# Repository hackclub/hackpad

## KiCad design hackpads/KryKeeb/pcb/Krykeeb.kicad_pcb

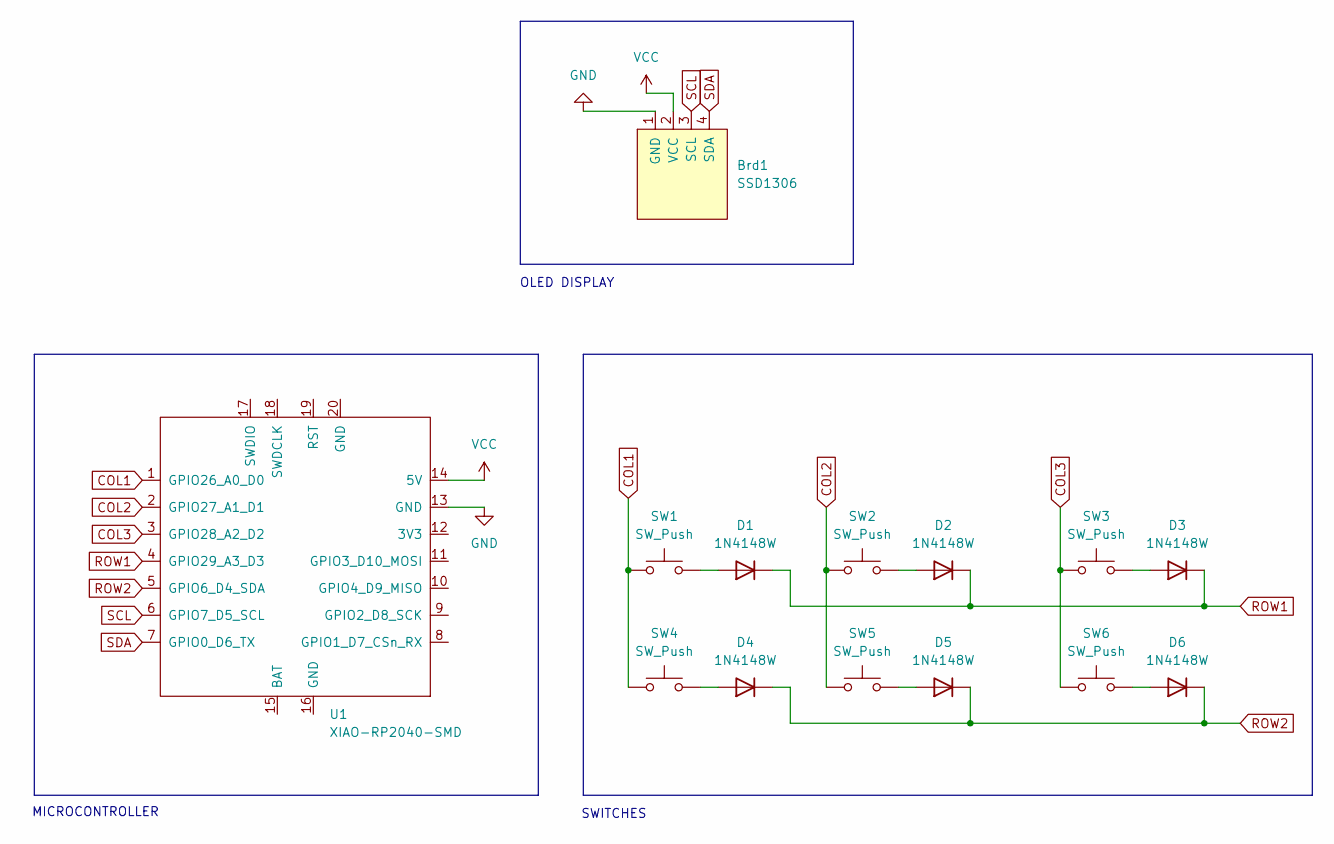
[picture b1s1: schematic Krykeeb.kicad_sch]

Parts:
Brd1: SSD1306; 128x64OLED
D1, D2, D3, D4, D5, D6: 1N4148W; D_A-405_P7.62mm_Horizontal
SW1, SW2, SW3, SW4, SW5, SW6: SW_Push; SW_Cherry_MX_1.00u_PCB
U1: XIAO-RP2040-SMD; MOUDLE14P-2.54-21X17.8MM

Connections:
COL1: SW1.1, SW4.1, U1.1 (GPIO26_A0_D0)
COL2: SW2.1, SW5.1, U1.2 (GPIO27_A1_D1)
COL3: SW3.1, SW6.1, U1.3 (GPIO28_A2_D2)
GND: Brd1.1 (GND), U1.13 (GND)
unnamed: D1.2 (A), SW1.2
unnamed: D2.2 (A), SW2.2
unnamed: D3.2 (A), SW3.2
unnamed: D4.2 (A), SW4.2
unnamed: D5.2 (A), SW5.2
unnamed: D6.2 (A), SW6.2
ROW1: D1.1 (K), D2.1 (K), D3.1 (K), U1.4 (GPIO29_A3_D3)
ROW2: D4.1 (K), D5.1 (K), D6.1 (K), U1.5 (GPIO6_D4_SDA)
SCL: Brd1.3 (SCL), U1.6 (GPIO7_D5_SCL)
SDA: Brd1.4 (SDA), U1.7 (GPIO0_D6_TX)
VCC: Brd1.2 (VCC), U1.14 (5V)

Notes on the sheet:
OLED DISPLAY
MICROCONTROLLER
SWITCHES

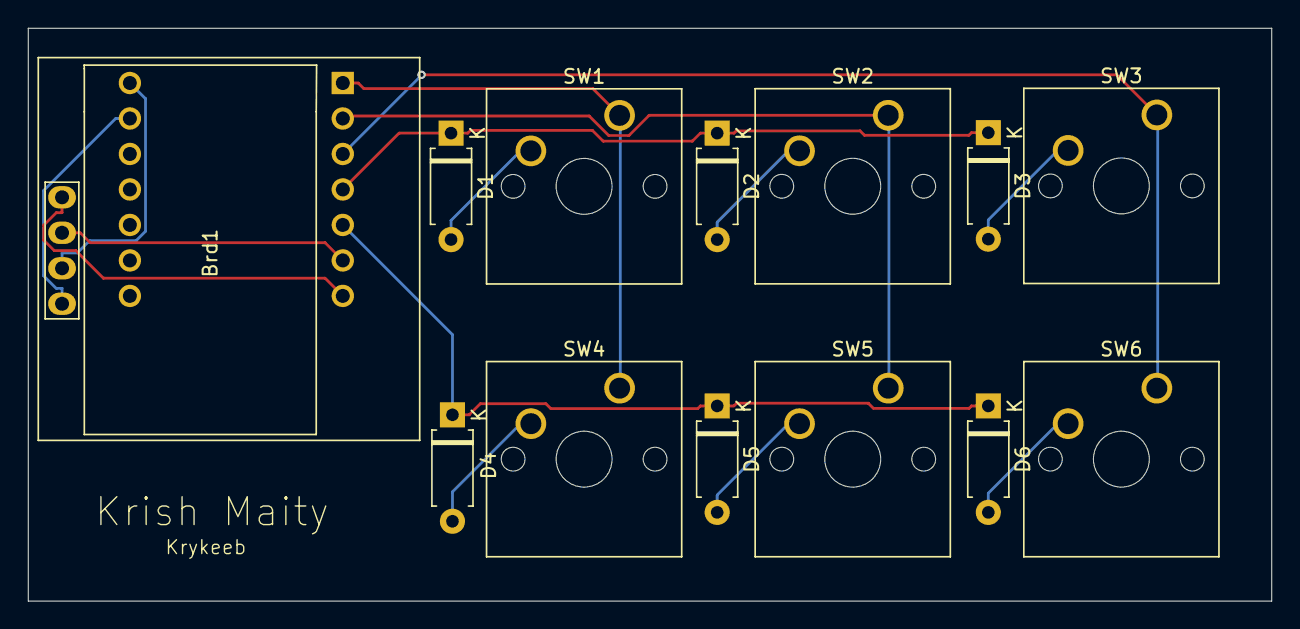
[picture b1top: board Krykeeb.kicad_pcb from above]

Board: 2 copper layers, 89.0 x 41.0 mm, 14 parts (1 on the bottom side), 15 nets.

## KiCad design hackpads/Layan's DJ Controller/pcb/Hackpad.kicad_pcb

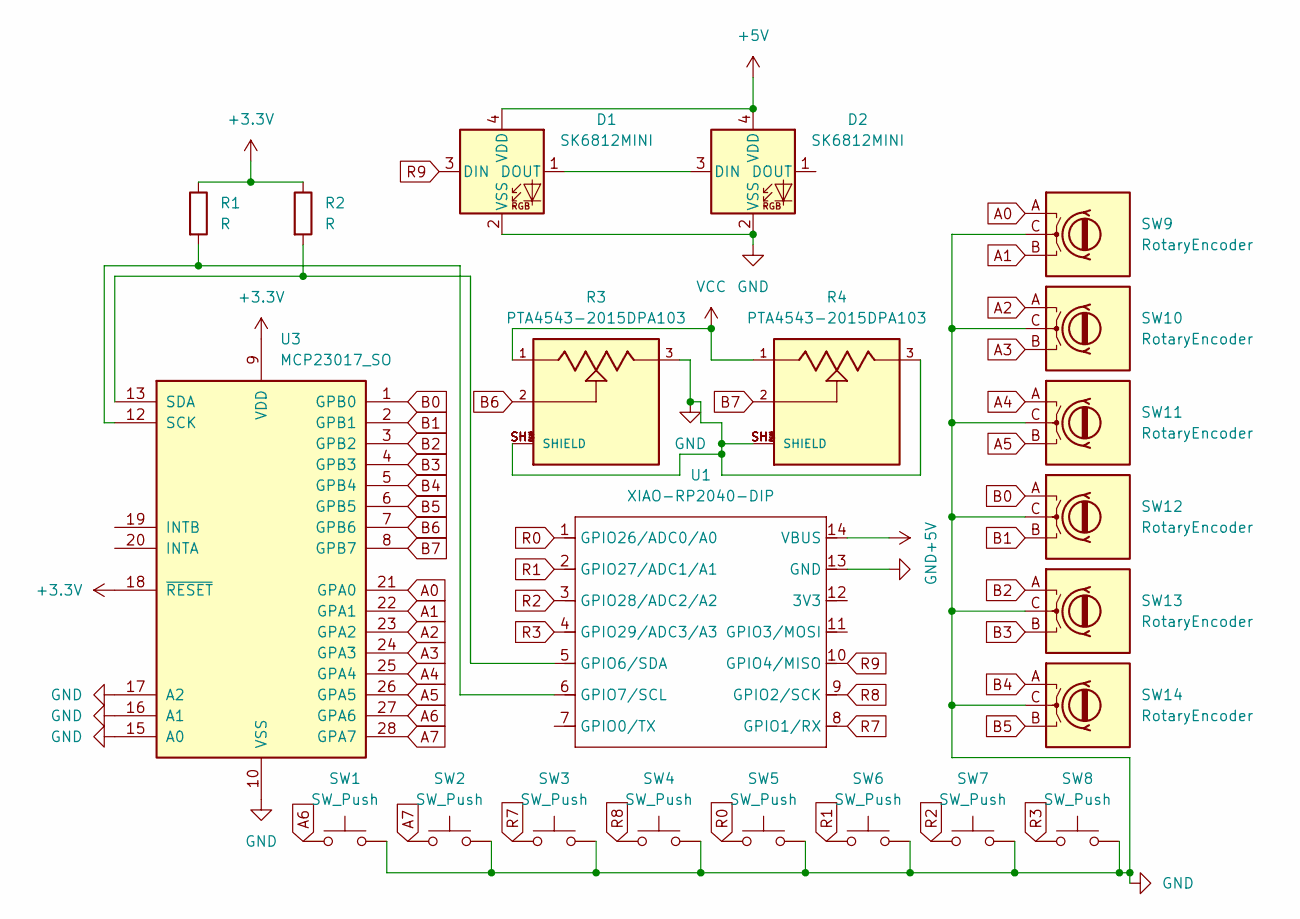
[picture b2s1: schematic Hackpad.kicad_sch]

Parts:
D1, D2: SK6812MINI; LED_SK6812MINI_PLCC4_3.5x3.5mm_P1.75mm
R1, R2: R; R_Axial_DIN0204_L3.6mm_D1.6mm_P7.62mm_Horizontal
R3, R4: PTA4543-2015DPA103; TRIM_PTA4543-2015DPA103; PARTREV 04/21
SW1, SW2, SW3, SW4, SW5, SW6, SW7, SW8: SW_Push; SW_Cherry_MX_1.00u_PCB
SW9, SW10, SW11, SW12, SW13, SW14: RotaryEncoder; RotaryEncoder_Alps_EC11E_Vertical_H20mm
U1: XIAO-RP2040-DIP
U3: MCP23017_SO; SOIC-28W_7.5x17.9mm_P1.27mm

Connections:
+3.3V: R1.1, R2.1, U3.9 (VDD), U3.18 (~RESET)
+5V: D1.4 (VDD), D2.4 (VDD), U1.14 (VBUS)
A0: SW9.A, U3.21 (GPA0)
A1: SW9.B, U3.22 (GPA1)
A2: SW10.A, U3.23 (GPA2)
A3: SW10.B, U3.24 (GPA3)
A4: SW11.A, U3.25 (GPA4)
A5: SW11.B, U3.26 (GPA5)
A6: SW1.1, U3.27 (GPA6)
A7: SW2.1, U3.28 (GPA7)
B0: SW12.A, U3.1 (GPB0)
B1: SW12.B, U3.2 (GPB1)
B2: SW13.A, U3.3 (GPB2)
B3: SW13.B, U3.4 (GPB3)
B4: SW14.A, U3.5 (GPB4)
B5: SW14.B, U3.6 (GPB5)
B6: R3.2, U3.7 (GPB6)
B7: R4.2, U3.8 (GPB7)
GND: D1.2 (VSS), D2.2 (VSS), R3.3, R3.SH1 (SHIELD), R3.SH2 (SHIELD), R3.SH3 (SHIELD), R3.SH4 (SHIELD), R4.3, R4.SH1 (SHIELD), R4.SH2 (SHIELD), R4.SH3 (SHIELD), R4.SH4 (SHIELD), SW1.2, SW2.2, SW3.2, SW4.2, SW5.2, SW6.2, SW7.2, SW8.2, SW9.C, SW10.C, SW11.C, SW12.C, SW13.C, SW14.C, U1.13 (GND), U3.10 (VSS), U3.15 (A0), U3.16 (A1), U3.17 (A2)
unnamed: D1.1 (DOUT), D2.3 (DIN)
unnamed: R2.2, U1.5 (GPIO6/SDA), U3.13 (SDA)
unnamed: R1.2, U1.6 (GPIO7/SCL), U3.12 (SCK)
R0: SW5.1, U1.1 (GPIO26/ADC0/A0)
R1: SW6.1, U1.2 (GPIO27/ADC1/A1)
R2: SW7.1, U1.3 (GPIO28/ADC2/A2)
R3: SW8.1, U1.4 (GPIO29/ADC3/A3)
R7: SW3.1, U1.8 (GPIO1/RX)
R8: SW4.1, U1.9 (GPIO2/SCK)
R9: D1.3 (DIN), U1.10 (GPIO4/MISO)
VCC: R3.1, R4.1

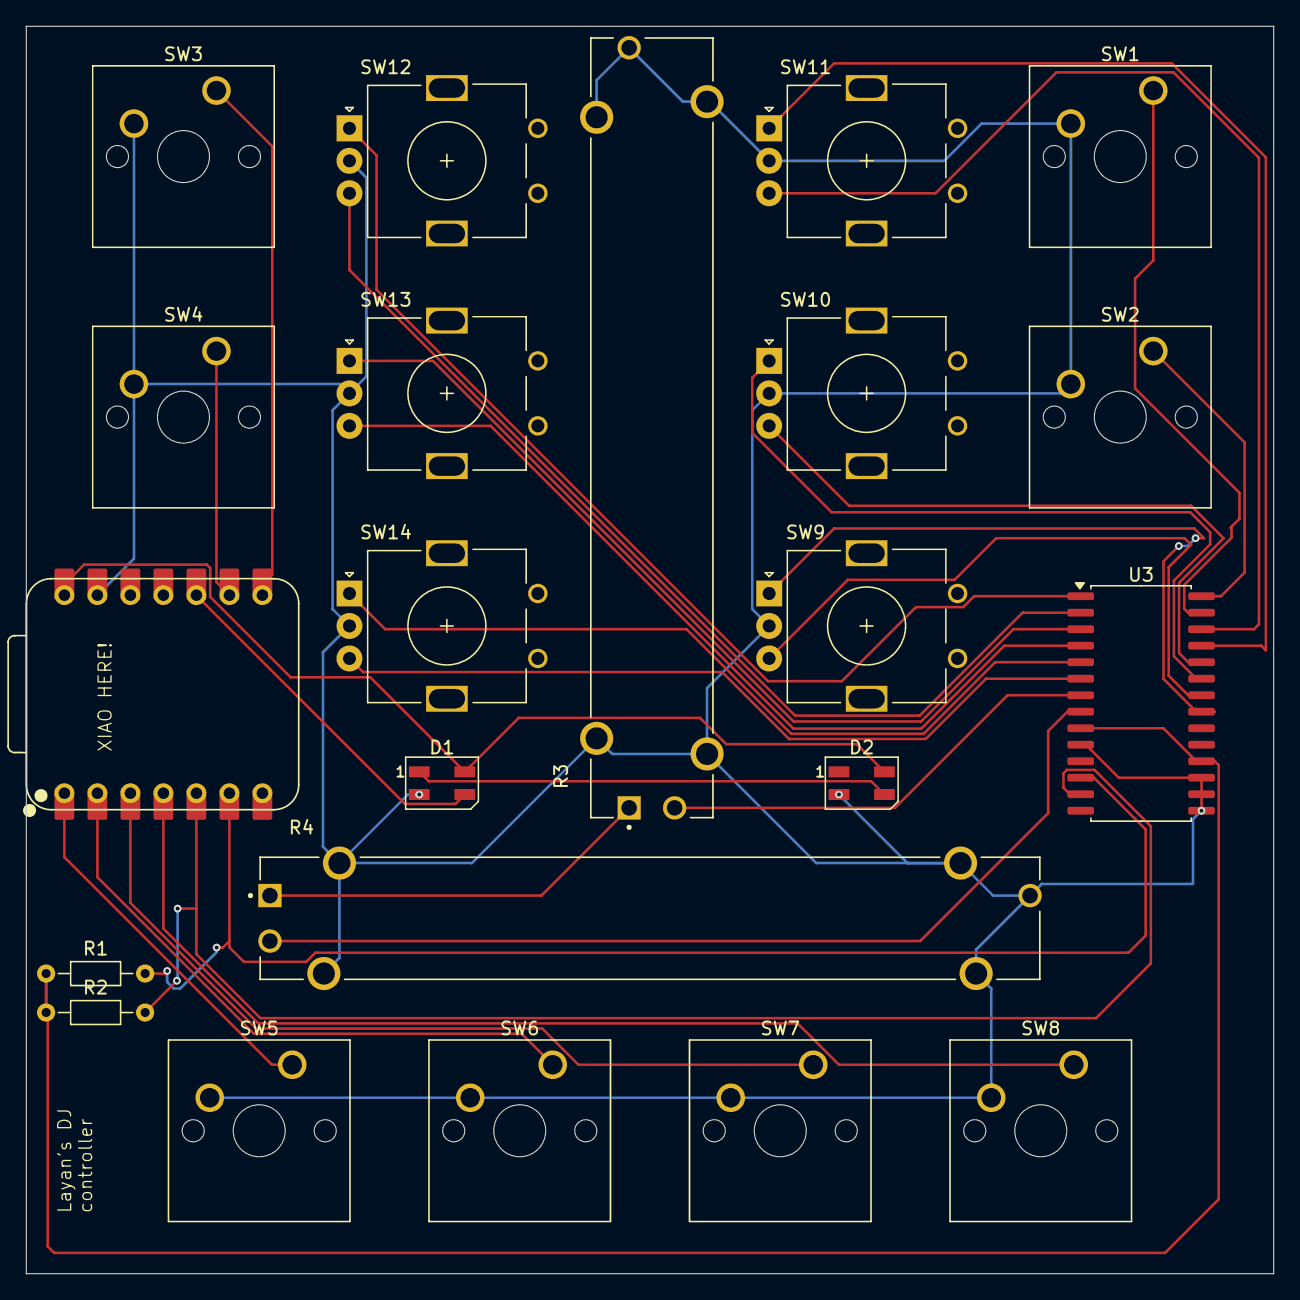
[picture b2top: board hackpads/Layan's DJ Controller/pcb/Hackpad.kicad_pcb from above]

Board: 2 copper layers, 96.0 x 96.0 mm, 22 parts (0 on the bottom side), 30 nets.

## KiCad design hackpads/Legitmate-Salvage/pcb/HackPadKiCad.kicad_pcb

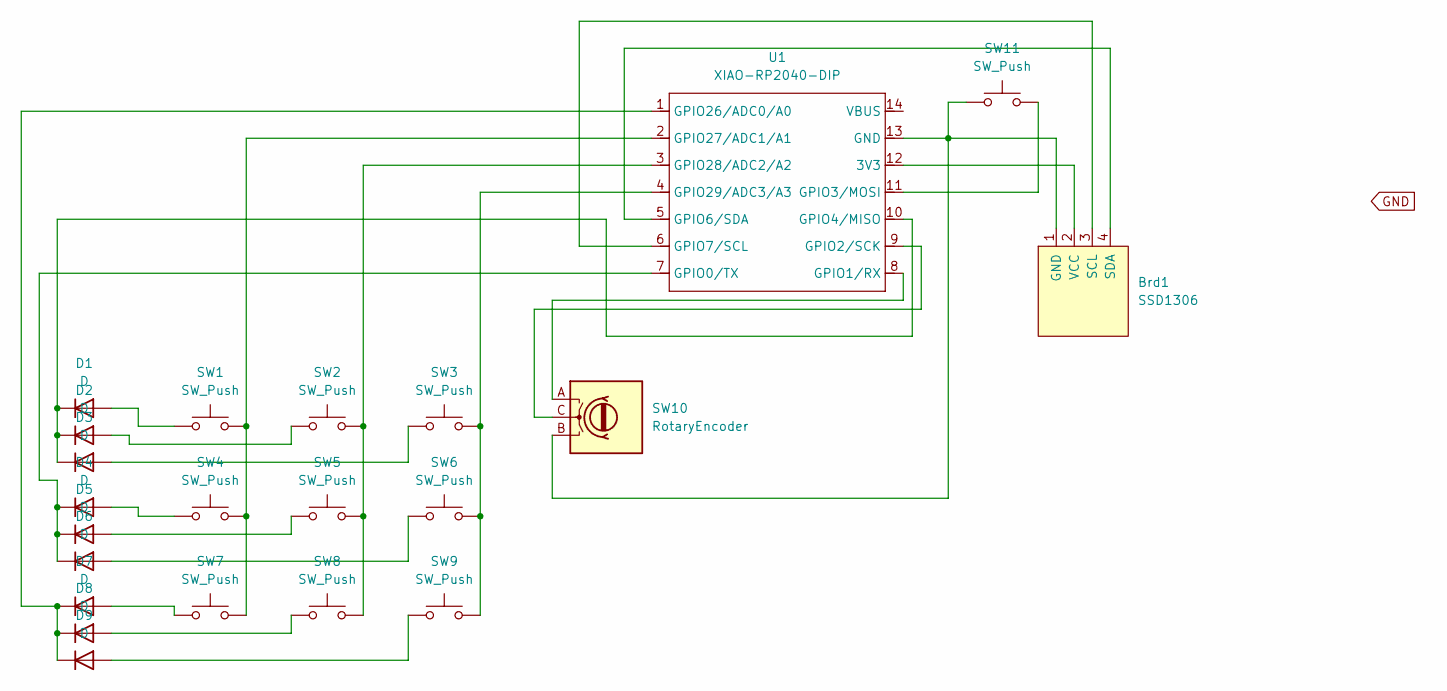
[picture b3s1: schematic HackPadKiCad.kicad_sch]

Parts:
Brd1: SSD1306; SSD1306-0.91-OLED-4pin-128x32
D1, D2, D3, D4, D5, D6, D7, D8, D9: D; D_DO-35_SOD27_P7.62mm_Horizontal
SW1, SW2, SW3, SW4, SW5, SW6, SW7, SW8, SW9, SW11: SW_Push; SW_Cherry_MX_1.00u_PCB
SW10: RotaryEncoder; RotaryEncoder_Alps_EC11E-Switch_Vertical_H20mm
U1: XIAO-RP2040-DIP; XIAO-ESP32C3-DIP

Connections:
unnamed: Brd1.1 (GND), SW10.B, SW11.1, U1.13 (GND)
unnamed: Brd1.3 (SCL), U1.6 (GPIO7/SCL)
unnamed: Brd1.4 (SDA), U1.5 (GPIO6/SDA)
unnamed: Brd1.2 (VCC), U1.12 (3V3)
unnamed: D1.2 (A), SW1.1
unnamed: D1.1 (K), D2.1 (K), D3.1 (K), U1.10 (GPIO4/MISO)
unnamed: D2.2 (A), SW2.1
unnamed: D3.2 (A), SW3.1
unnamed: D4.2 (A), SW4.1
unnamed: D4.1 (K), D5.1 (K), D6.1 (K), U1.7 (GPIO0/TX)
unnamed: D5.2 (A), SW5.1
unnamed: D6.2 (A), SW6.1
unnamed: D7.2 (A), SW7.1
unnamed: D7.1 (K), D8.1 (K), D9.1 (K), U1.1 (GPIO26/ADC0/A0)
unnamed: D8.2 (A), SW8.1
unnamed: D9.2 (A), SW9.1
unnamed: SW10.A, U1.8 (GPIO1/RX)
unnamed: SW10.C, U1.9 (GPIO2/SCK)
unnamed: SW11.2, U1.11 (GPIO3/MOSI)
unnamed: SW1.2, SW4.2, SW7.2, U1.2 (GPIO27/ADC1/A1)
unnamed: SW2.2, SW5.2, SW8.2, U1.3 (GPIO28/ADC2/A2)
unnamed: SW3.2, SW6.2, SW9.2, U1.4 (GPIO29/ADC3/A3)

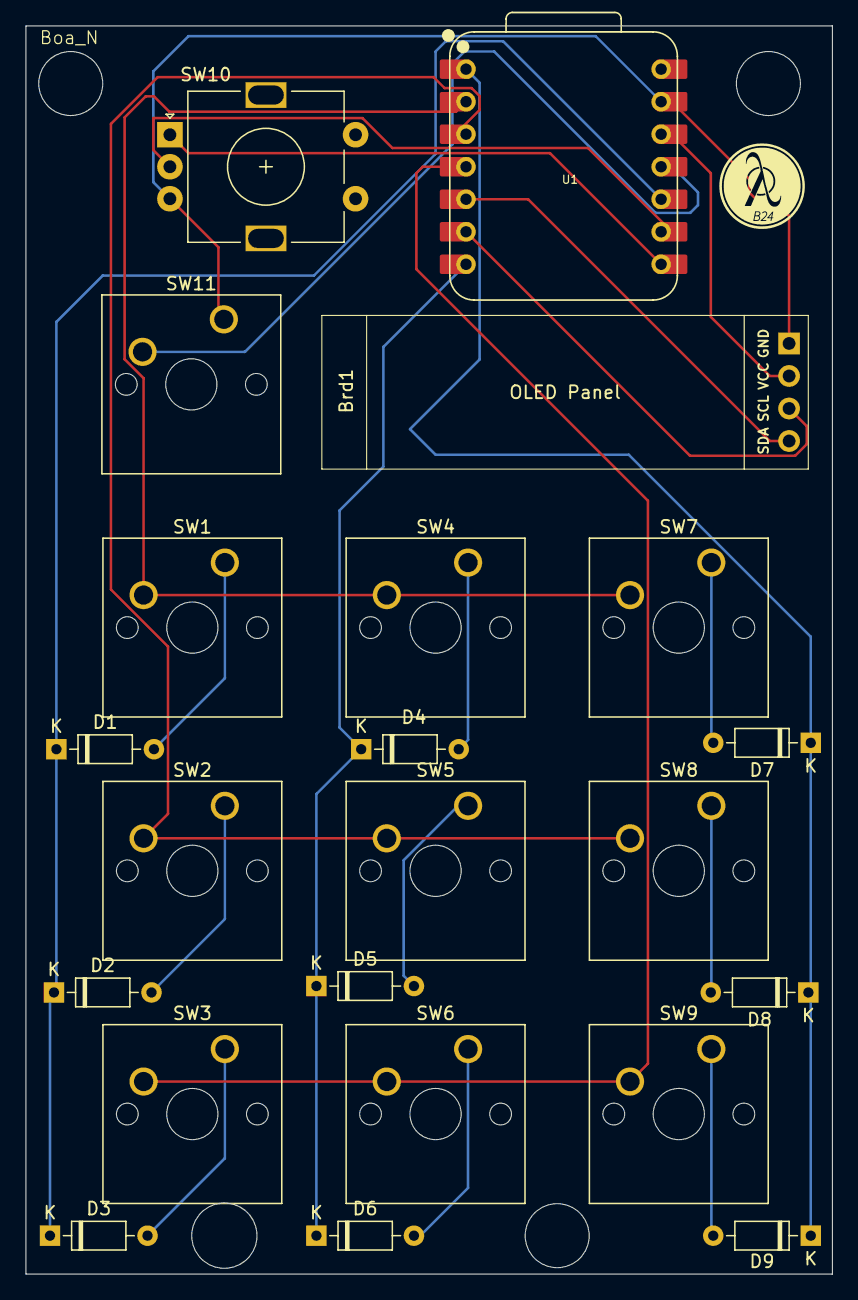
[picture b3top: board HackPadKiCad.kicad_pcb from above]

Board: 2 copper layers, 63.0 x 97.5 mm, 22 parts (0 on the bottom side), 22 nets.

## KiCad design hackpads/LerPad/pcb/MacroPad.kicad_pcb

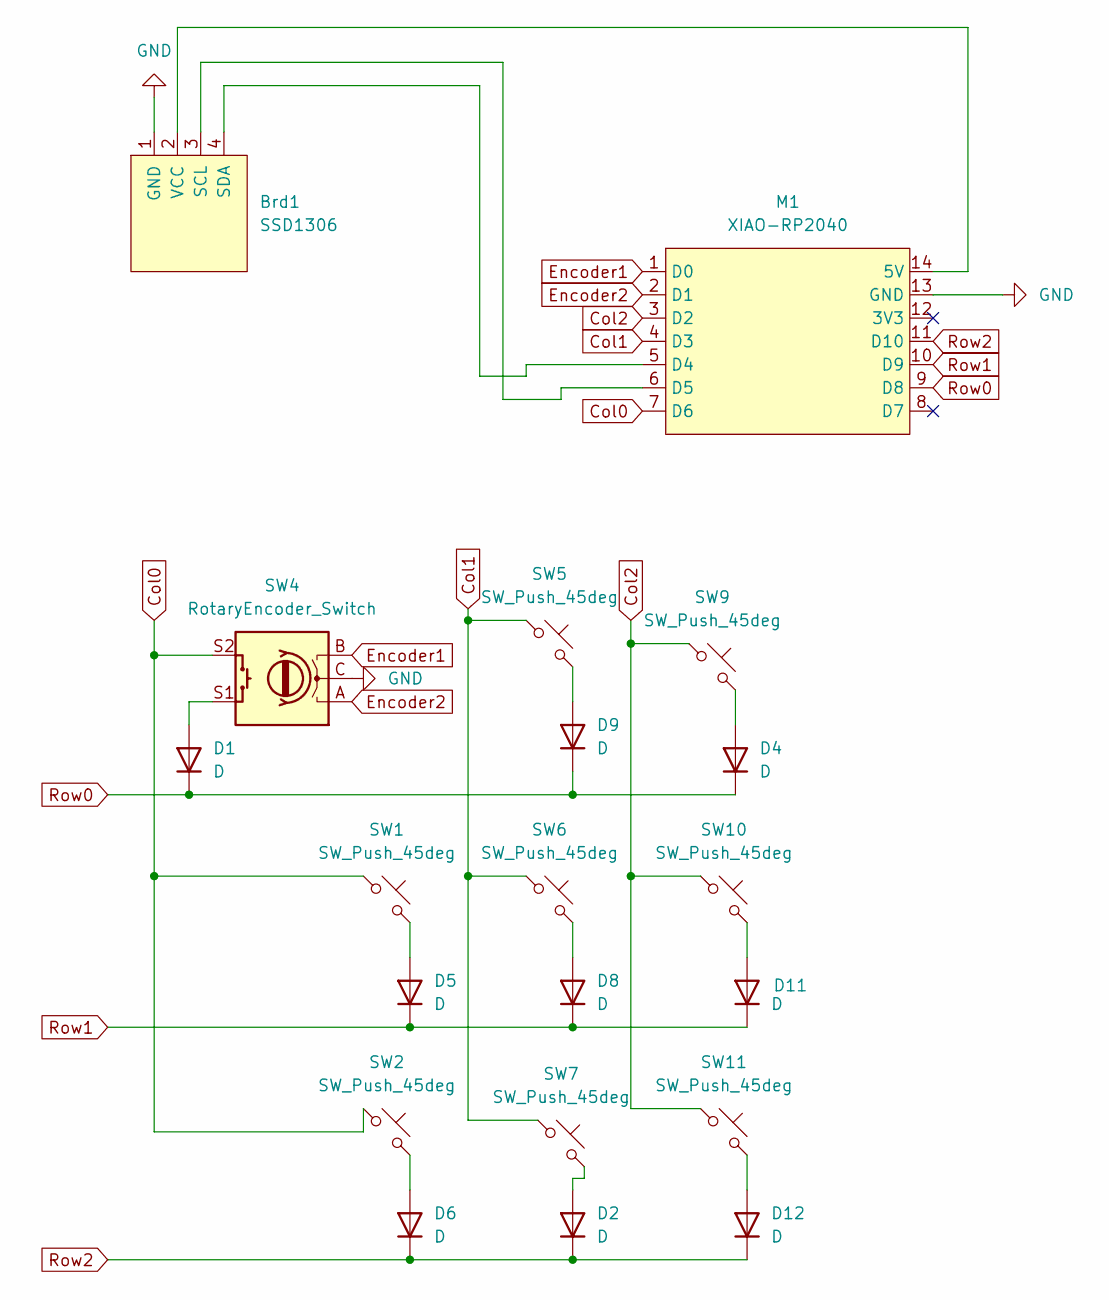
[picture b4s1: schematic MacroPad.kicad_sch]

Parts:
Brd1: SSD1306; SSD1306-0.91-OLED-4pin-128x32
D1, D2, D4, D5, D6, D8, D9, D11, D12: D; 1N4148
M1: XIAO-RP2040
SW1, SW2, SW5, SW6, SW7, SW9, SW10, SW11: SW_Push_45deg; MX-Solderable-1U
SW4: RotaryEncoder_Switch; RotaryEncoder_Alps_EC11E-Switch_Vertical_H20mm

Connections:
Col0: M1.7 (D6), SW1.1, SW2.1, SW4.S2
Col1: M1.4 (D3), SW5.1, SW6.1, SW7.1
Col2: M1.3 (D2), SW9.1, SW10.1, SW11.1
Encoder1: M1.1 (D0), SW4.B
Encoder2: M1.2 (D1), SW4.A
GND: Brd1.1 (GND), M1.13 (GND), SW4.C
unnamed: Brd1.3 (SCL), M1.6 (D5)
unnamed: Brd1.4 (SDA), M1.5 (D4)
unnamed: Brd1.2 (VCC), M1.14 (5V)
unnamed: D1.2 (A), SW4.S1
unnamed: D2.2 (A), SW7.2
unnamed: D4.2 (A), SW9.2
unnamed: D5.2 (A), SW1.2
unnamed: D6.2 (A), SW2.2
unnamed: D8.2 (A), SW6.2
unnamed: D9.2 (A), SW5.2
unnamed: D11.2 (A), SW10.2
unnamed: D12.2 (A), SW11.2
Row0: D1.1 (K), D4.1 (K), D9.1 (K), M1.9 (D8)
Row1: D5.1 (K), D8.1 (K), D11.1 (K), M1.10 (D9)
Row2: D2.1 (K), D6.1 (K), D12.1 (K), M1.11 (D10)

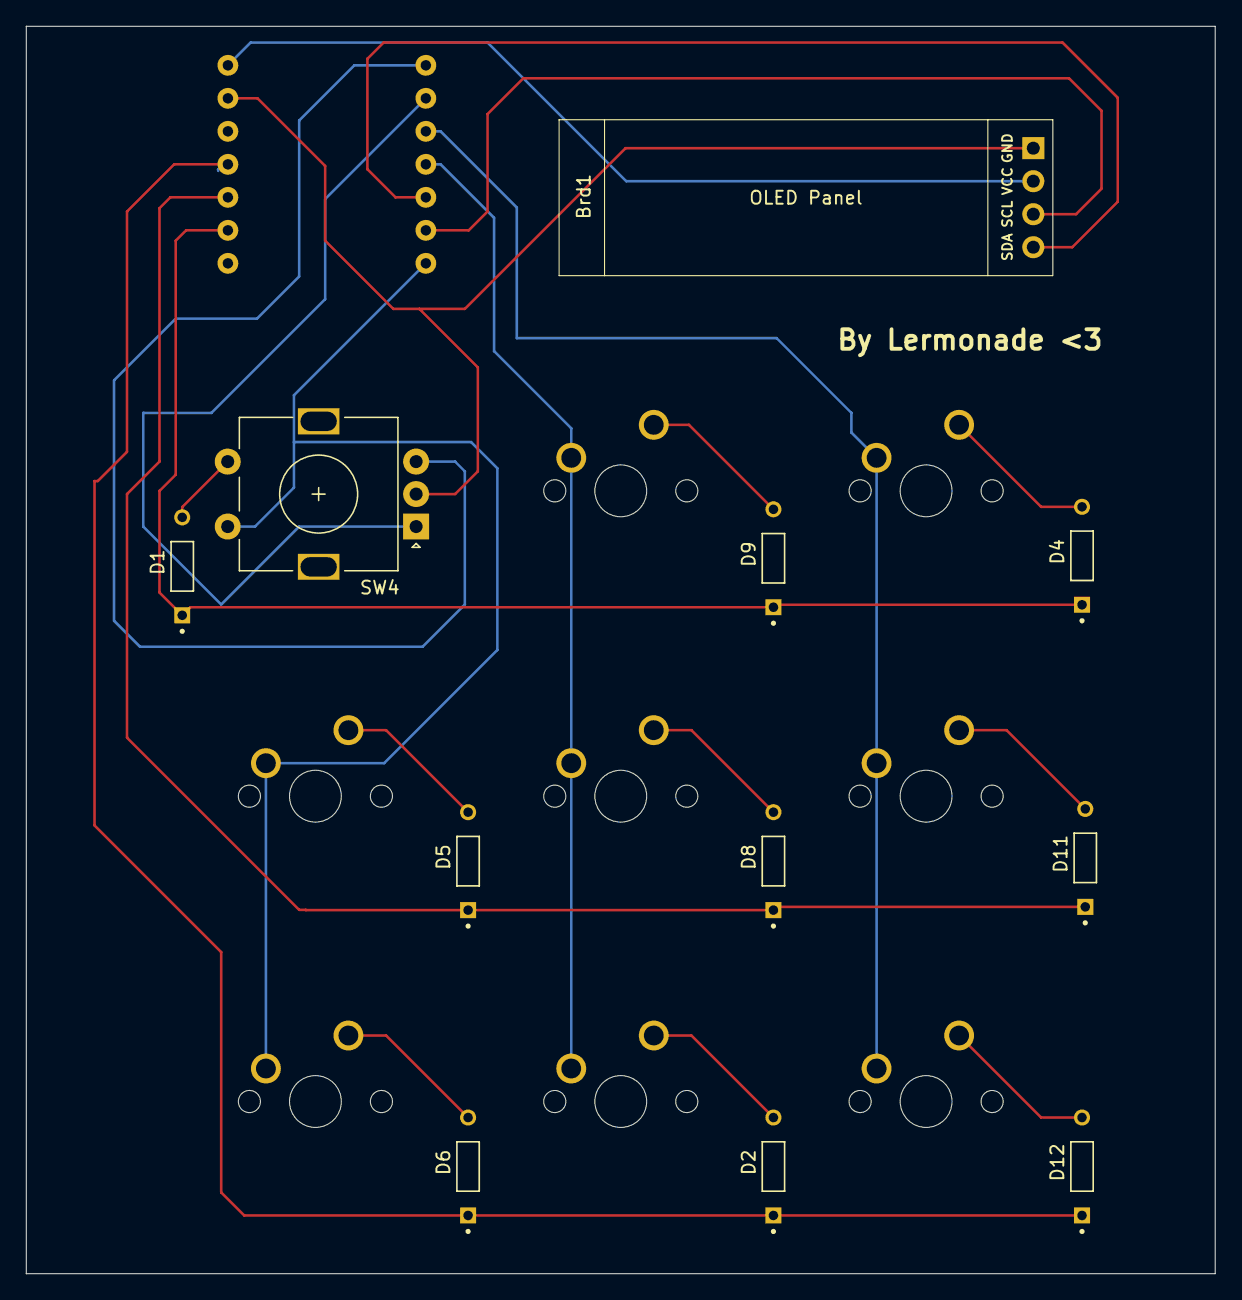
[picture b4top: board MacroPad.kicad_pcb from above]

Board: 2 copper layers, 91.5 x 96.0 mm, 20 parts (1 on the bottom side), 21 nets.

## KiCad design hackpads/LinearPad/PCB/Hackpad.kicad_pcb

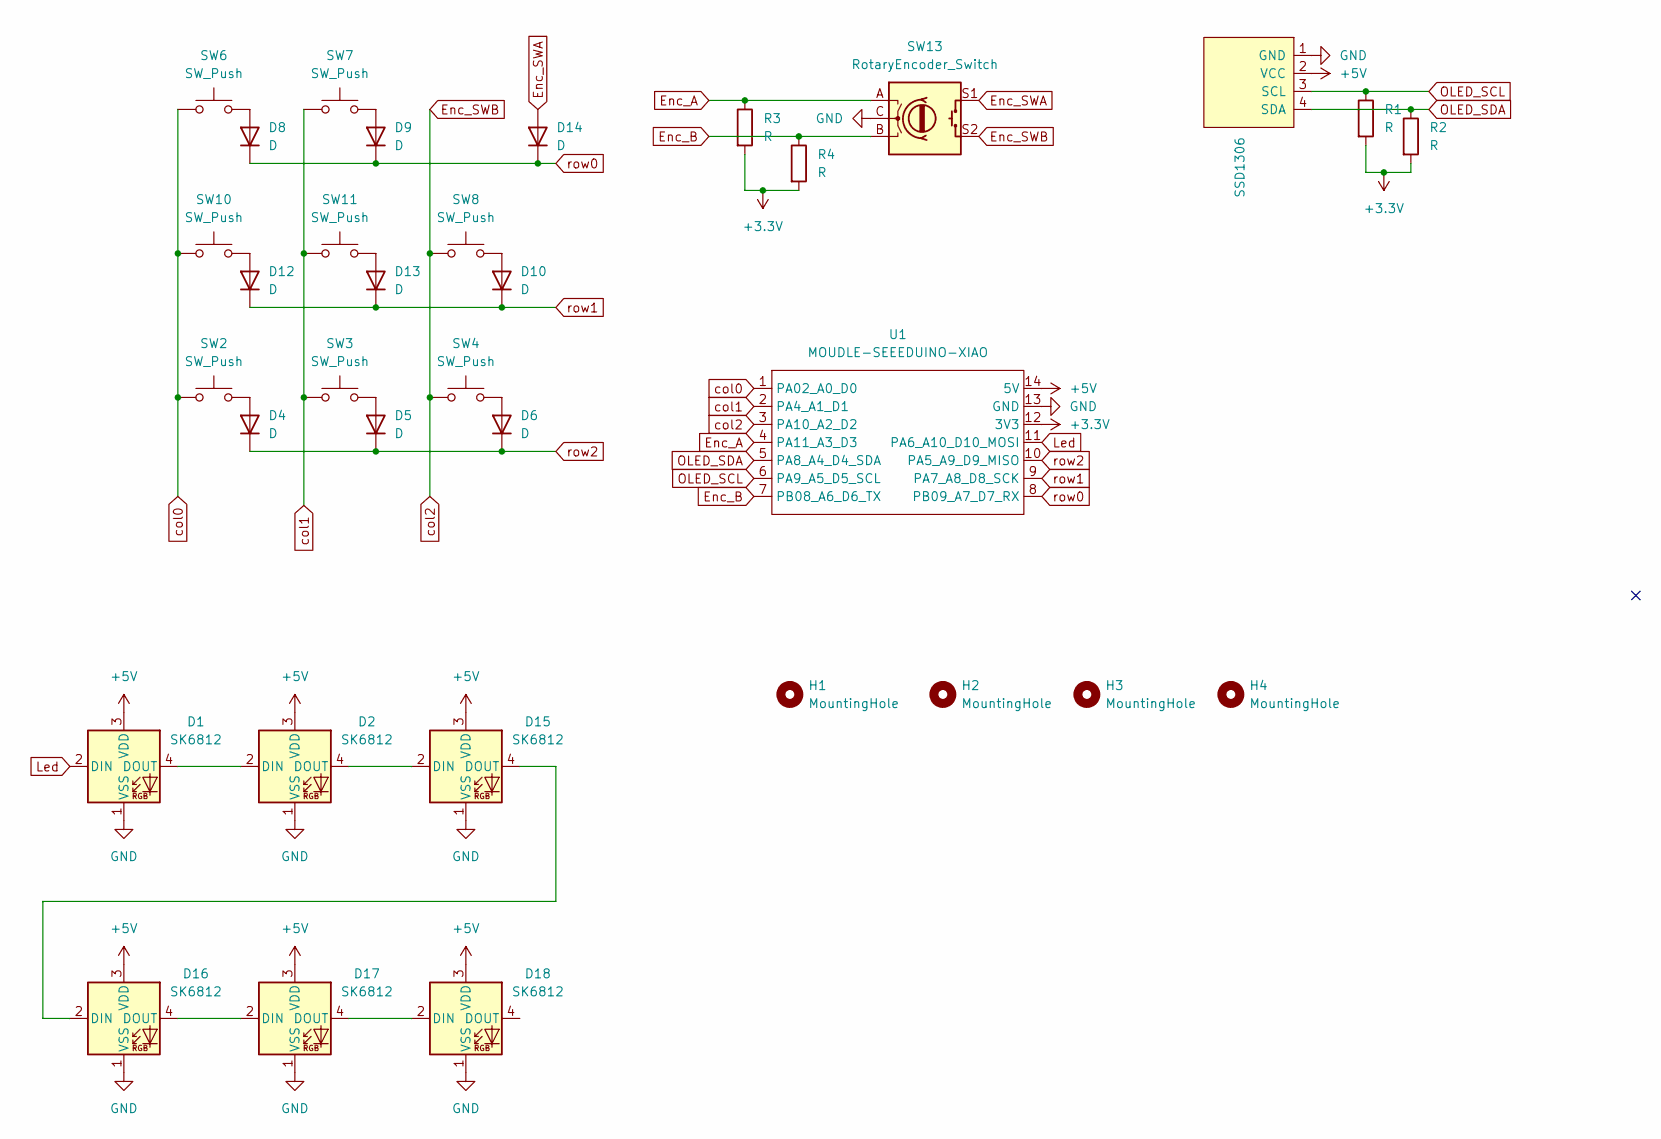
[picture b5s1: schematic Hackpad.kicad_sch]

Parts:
Brd1: SSD1306; 128x64OLED
D1, D2, D15, D16, D17, D18: SK6812; LED_SK6812_PLCC4_5.0x5.0mm_P3.2mm
D4, D5, D6, D8, D9, D10, D12, D13, D14: D; D_DO-35_SOD27_P7.62mm_Horizontal
H1, H2, H3, H4: MountingHole; MountingHole_3.2mm_M3
R1, R2, R3, R4: R; R_Axial_DIN0204_L3.6mm_D1.6mm_P7.62mm_Horizontal
SW2, SW3, SW4, SW6, SW7, SW8, SW10, SW11: SW_Push; MX-Solderable-1U
SW13: RotaryEncoder_Switch; RotaryEncoder_Alps_EC11E-Switch_Vertical_H20mm
U1: MOUDLE-SEEEDUINO-XIAO; XIAO-Generic-Hybrid-14P-2.54-21X17.8MM

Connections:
+3.3V: R1.2, R2.2, R3.2, R4.2, U1.12 (3V3)
+5V: Brd1.2 (VCC), D1.3 (VDD), D2.3 (VDD), D15.3 (VDD), D16.3 (VDD), D17.3 (VDD), D18.3 (VDD), U1.14 (5V)
Enc_A: R3.1, SW13.A, U1.4 (PA11_A3_D3)
Enc_B: R4.1, SW13.B, U1.7 (PB08_A6_D6_TX)
Enc_SWA: D14.2 (A), SW13.S1
Enc_SWB: SW4.1, SW8.1, SW13.S2, U1.3 (PA10_A2_D2)
GND: Brd1.1 (GND), D1.1 (VSS), D2.1 (VSS), D15.1 (VSS), D16.1 (VSS), D17.1 (VSS), D18.1 (VSS), SW13.C, U1.13 (GND)
Led: D1.2 (DIN), U1.11 (PA6_A10_D10_MOSI)
unnamed: D1.4 (DOUT), D2.2 (DIN)
unnamed: D4.2 (A), SW2.2
unnamed: D5.2 (A), SW3.2
unnamed: D6.2 (A), SW4.2
unnamed: D8.2 (A), SW6.2
unnamed: D9.2 (A), SW7.2
unnamed: D10.2 (A), SW8.2
unnamed: D12.2 (A), SW10.2
unnamed: D13.2 (A), SW11.2
unnamed: D2.4 (DOUT), D15.2 (DIN)
unnamed: D15.4 (DOUT), D16.2 (DIN)
unnamed: D16.4 (DOUT), D17.2 (DIN)
unnamed: D17.4 (DOUT), D18.2 (DIN)
OLED_SCL: Brd1.3 (SCL), R1.1, U1.6 (PA9_A5_D5_SCL)
OLED_SDA: Brd1.4 (SDA), R2.1, U1.5 (PA8_A4_D4_SDA)
col0: SW2.1, SW6.1, SW10.1, U1.1 (PA02_A0_D0)
col1: SW3.1, SW7.1, SW11.1, U1.2 (PA4_A1_D1)
row0: D8.1 (K), D9.1 (K), D14.1 (K), U1.8 (PB09_A7_D7_RX)
row1: D10.1 (K), D12.1 (K), D13.1 (K), U1.9 (PA7_A8_D8_SCK)
row2: D4.1 (K), D5.1 (K), D6.1 (K), U1.10 (PA5_A9_D9_MISO)

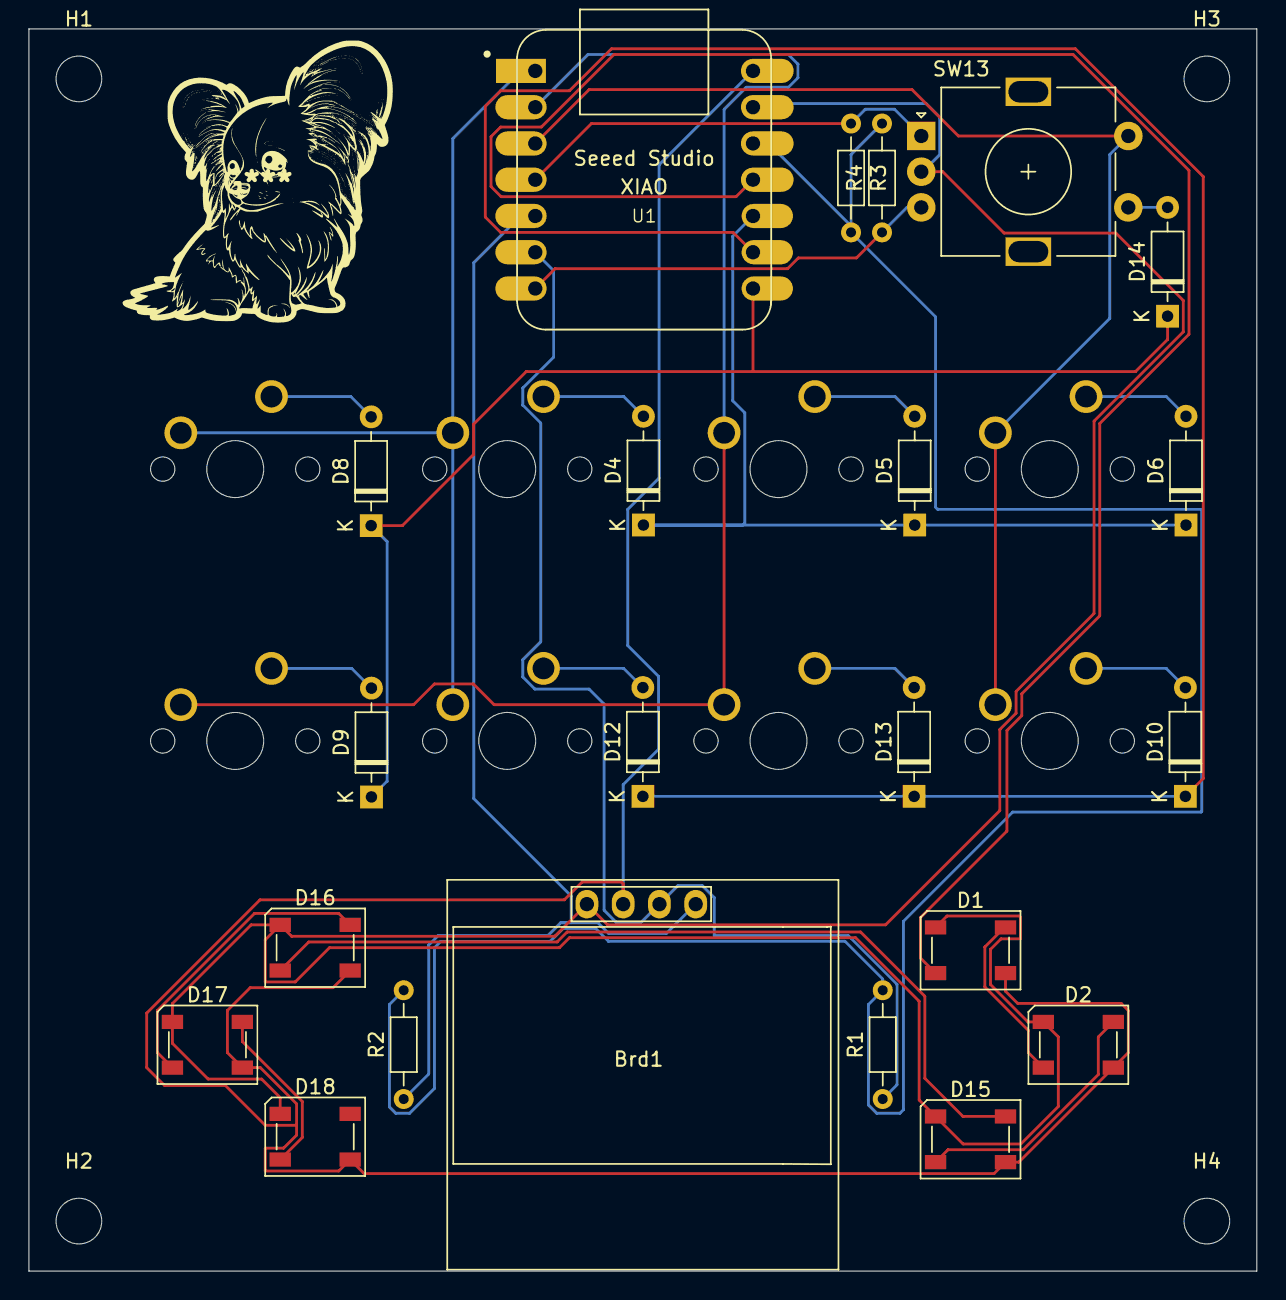
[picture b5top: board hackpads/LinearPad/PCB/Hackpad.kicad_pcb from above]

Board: 2 copper layers, 86.0 x 87.0 mm, 34 parts (0 on the bottom side), 28 nets.

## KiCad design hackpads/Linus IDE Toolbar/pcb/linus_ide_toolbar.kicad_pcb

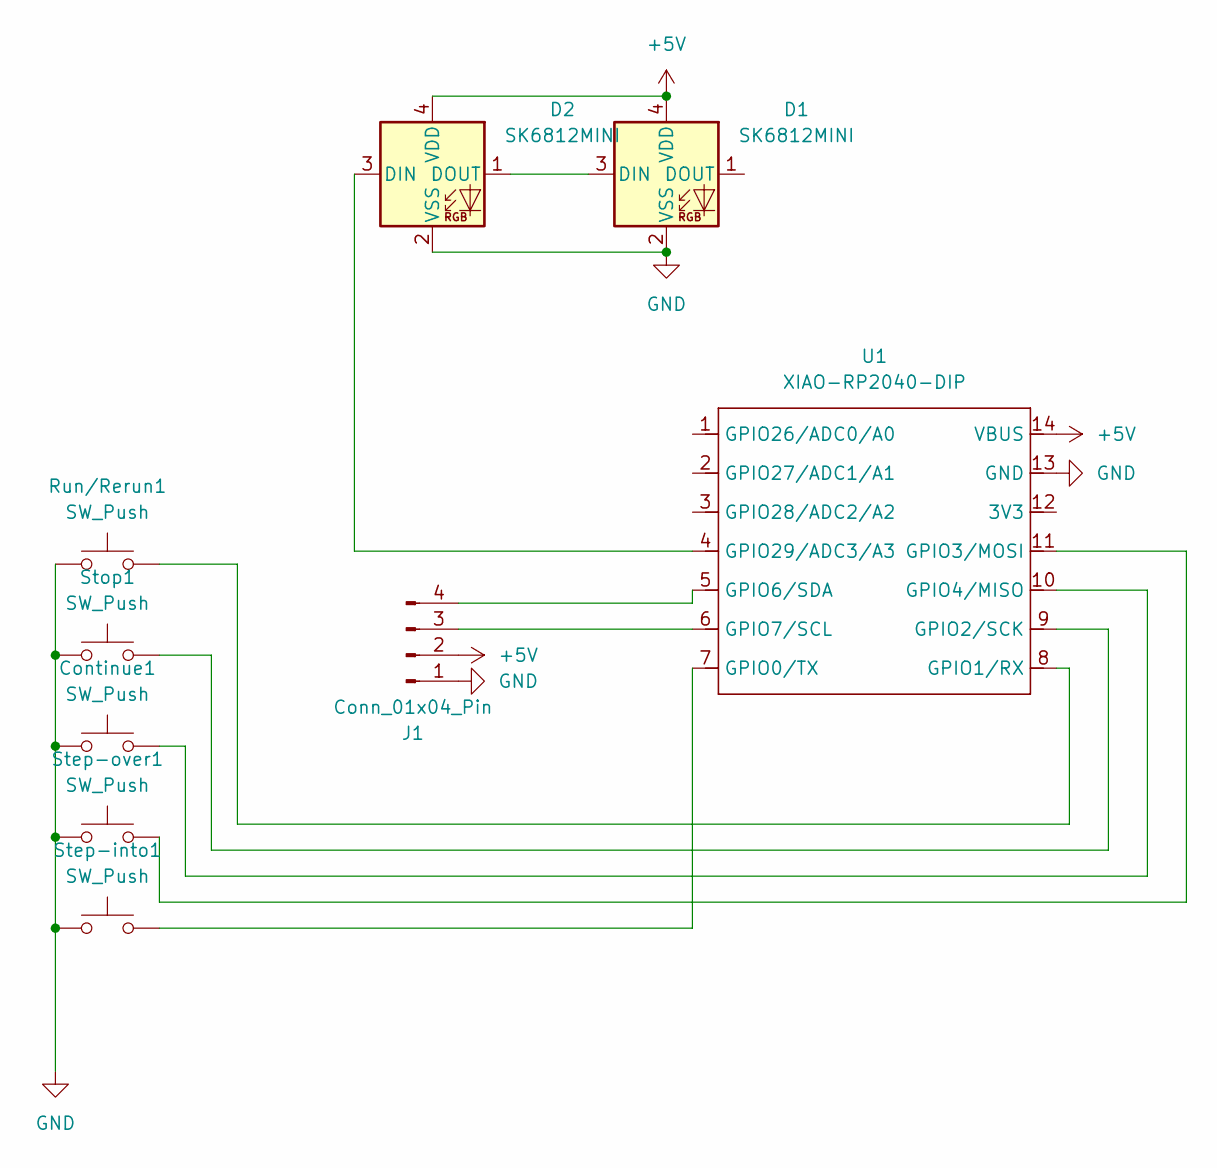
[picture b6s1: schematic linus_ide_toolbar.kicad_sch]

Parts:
Continue1: SW_Push; SW_Cherry_MX_1.00u_PCB
D1, D2: SK6812MINI; LED_SK6812MINI_PLCC4_3.5x3.5mm_P1.75mm
J1: Conn_01x04_Pin; SSD1306-0.91-OLED-4pin-128x32
Run/Rerun1: SW_Push; SW_Cherry_MX_1.00u_PCB
Step-into1: SW_Push; SW_Cherry_MX_1.00u_PCB
Step-over1: SW_Push; SW_Cherry_MX_1.00u_PCB
Stop1: SW_Push; SW_Cherry_MX_1.00u_PCB
U1: XIAO-RP2040-DIP

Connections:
+5V: D1.4 (VDD), D2.4 (VDD), J1.2, U1.14 (VBUS)
GND: Continue1.1, D1.2 (VSS), D2.2 (VSS), J1.1, Run/Rerun1.1, Step-into1.1, Step-over1.1, Stop1.1, U1.13 (GND)
unnamed: D1.3 (DIN), D2.1 (DOUT)
unnamed: D2.3 (DIN), U1.4 (GPIO29/ADC3/A3)
unnamed: J1.3, U1.6 (GPIO7/SCL)
unnamed: J1.4, U1.5 (GPIO6/SDA)
unnamed: Step-into1.2, U1.7 (GPIO0/TX)
unnamed: Run/Rerun1.2, U1.8 (GPIO1/RX)
unnamed: Stop1.2, U1.9 (GPIO2/SCK)
unnamed: Step-over1.2, U1.11 (GPIO3/MOSI)
unnamed: Continue1.2, U1.10 (GPIO4/MISO)

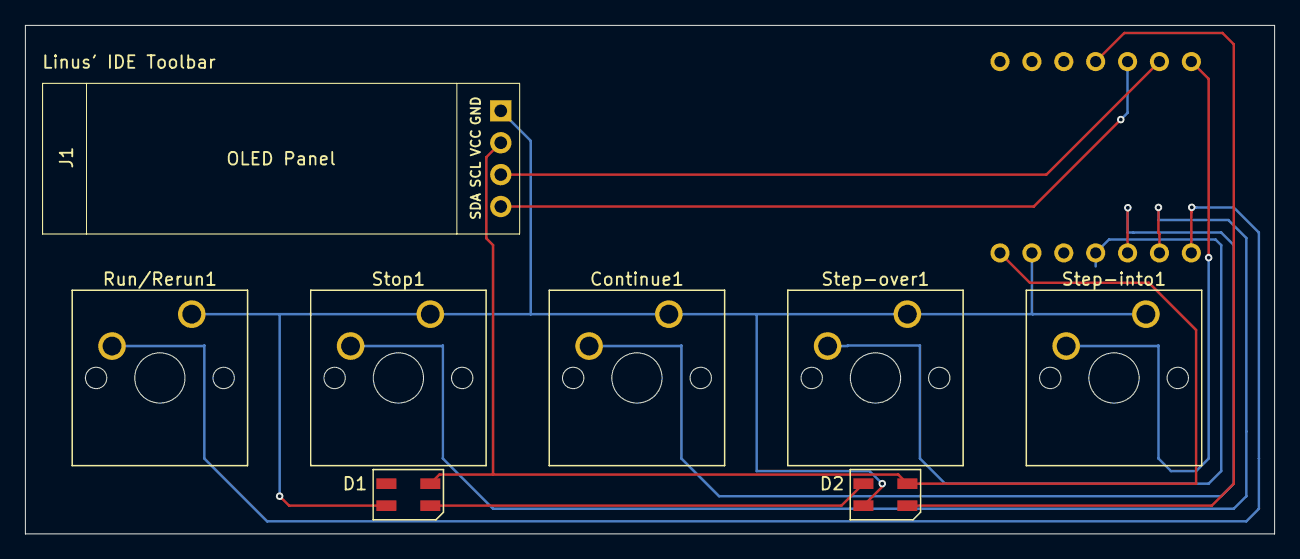
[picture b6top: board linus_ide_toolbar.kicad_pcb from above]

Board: 2 copper layers, 99.5 x 40.5 mm, 9 parts (1 on the bottom side), 11 nets.

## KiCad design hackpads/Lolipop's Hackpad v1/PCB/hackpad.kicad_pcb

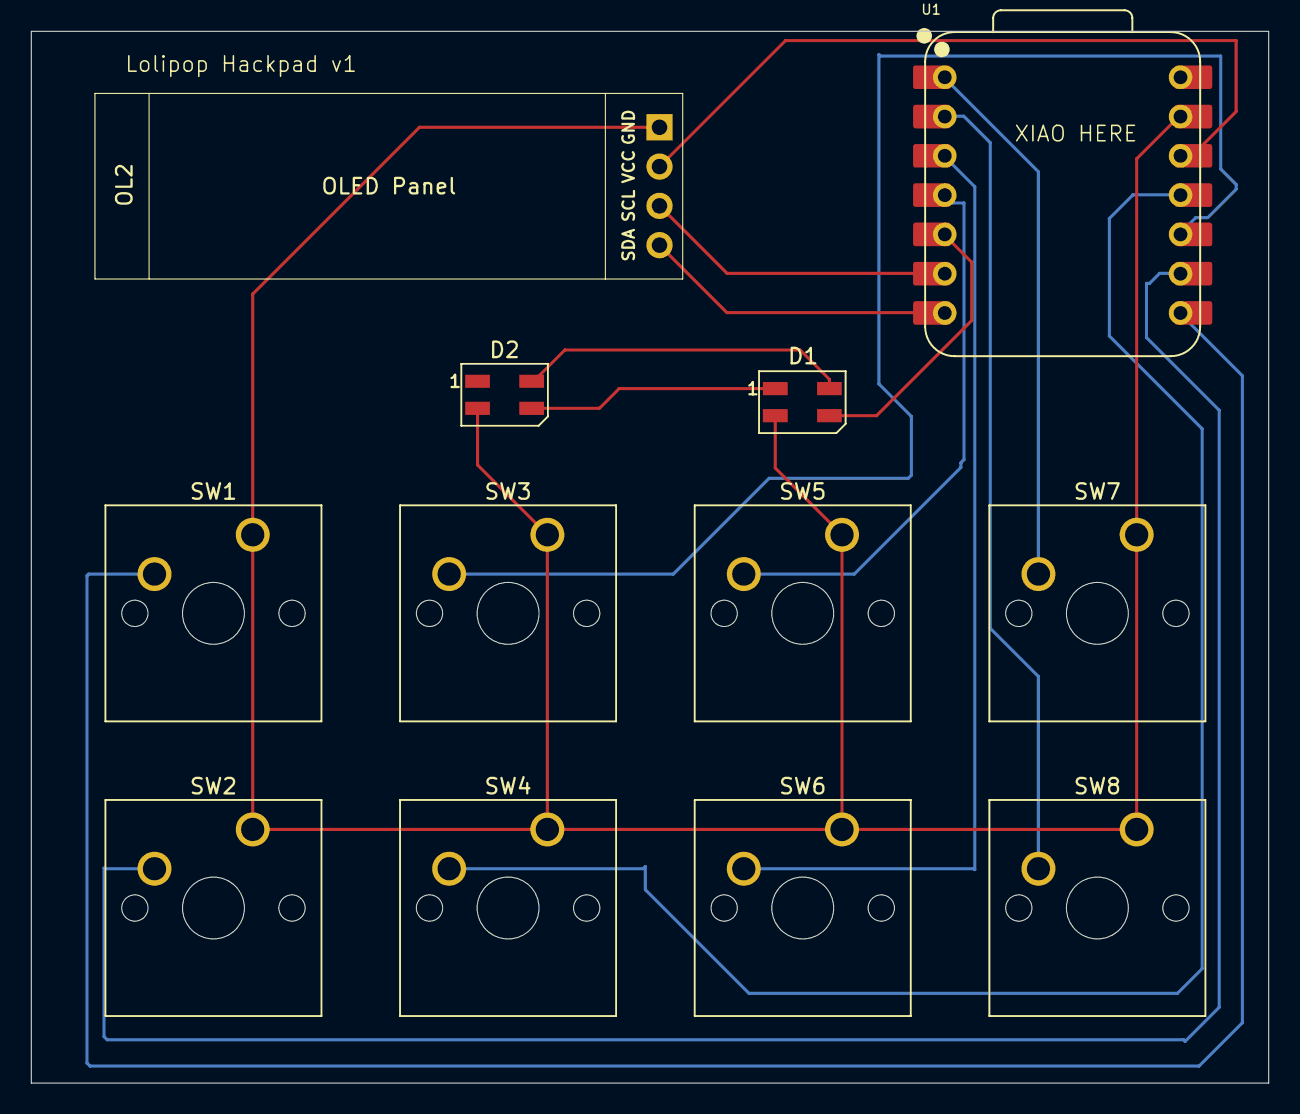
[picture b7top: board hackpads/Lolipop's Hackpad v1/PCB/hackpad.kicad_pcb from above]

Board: 2 copper layers, 80.0 x 68.0 mm, 12 parts (0 on the bottom side), 15 nets.

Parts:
D1, D2: SK6812MINI; LED_SK6812MINI_PLCC4_3.5x3.5mm_P1.75mm
OL2: OLED; SSD1306-0.91-OLED-4pin-128x32
SW1, SW2, SW3, SW4, SW5, SW6, SW7, SW8: SW_Push; SW_Cherry_MX_1.00u_PCB
U1: XIAO-RP2040-DIP

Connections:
GND: D1.2 (VSS), D2.2 (VSS), OL2.1 (SDA), SW1.1, SW2.1, SW3.1, SW4.1, SW5.1, SW6.1, SW7.1, SW8.1, U1.13 (GND)
unnamed: D1.3 (DIN), U1.5 (GPIO6/SDA)
unnamed: D1.1 (DOUT), D2.3 (DIN)
unnamed: D1.4 (VDD), D2.4 (VDD)
unnamed: OL2.3 (VCC), U1.6 (GPIO7/SCL)
unnamed: OL2.4 (GND), U1.7 (GPIO0/TX)
unnamed: OL2.2 (SCL), U1.12 (3V3)
unnamed: SW1.2, U1.8 (GPIO1/RX)
unnamed: SW2.2, U1.9 (GPIO2/SCK)
unnamed: SW4.2, U1.11 (GPIO3/MOSI)
unnamed: SW3.2, U1.10 (GPIO4/MISO)
unnamed: SW7.2, U1.1 (GPIO26/ADC0/A0)
unnamed: SW8.2, U1.2 (GPIO27/ADC1/A1)
unnamed: SW6.2, U1.3 (GPIO28/ADC2/A2)
unnamed: SW5.2, U1.4 (GPIO29/ADC3/A3)
